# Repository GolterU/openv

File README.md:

### Heizungssteuerung und -überwachung per Optolink-Schnittstelle
Für die Windows-Software ["Viess-ion"](https://github.com/openv/openv/wiki/Vies-sion) werden hier die passenden Parameter-Dateien bearbeitet, damit sie zur Heizungsanlage passen. Die Kommunikation zwischen Steuer-PC und der Heizung erfolgt mithilfe des Adapters ["Optolink-Duo/Sniffer"](https://github.com/openv/openv/wiki/Bauanleitung-USB_Duo-Sniffer).<p>
Die Heizungsanlage besteht aus dem Gaswandgerät "Vitodens 300-W" WB3C, Code: CB und zwei Heizkreisen. <br>
Kreis A1 für die Heizkörper hängt über die interne Heizungspumpe direkt am Kessel. Kreis M2 für die Räume mit Fußbodenheizung über einen Drei-Wege-Mischer, der am KM-Bus angeschlossen ist. Es wird zusätzlich ein 300-Liter-Boiler zur Warmwasserbereitung betrieben. Die Warmwasserverteilung im Haus erfolgt mit Hilfe einer zeitgesteuerten Zirkulationspumpe, die ihrerseits an der externen Erweiterung H1 hängt.<br>
Die Heizungssteuerung erfolgt intern mit der herstellereigenen Vitotronic. Die Heizkreise des Hauses jedoch über eine selbstentwickelte Steuerung ["HSC"](https://godemann.de/Controller/Hauscomputer/hauscomputer.html), die ohne Eingriff in die Heizungssteuerung auskommt.

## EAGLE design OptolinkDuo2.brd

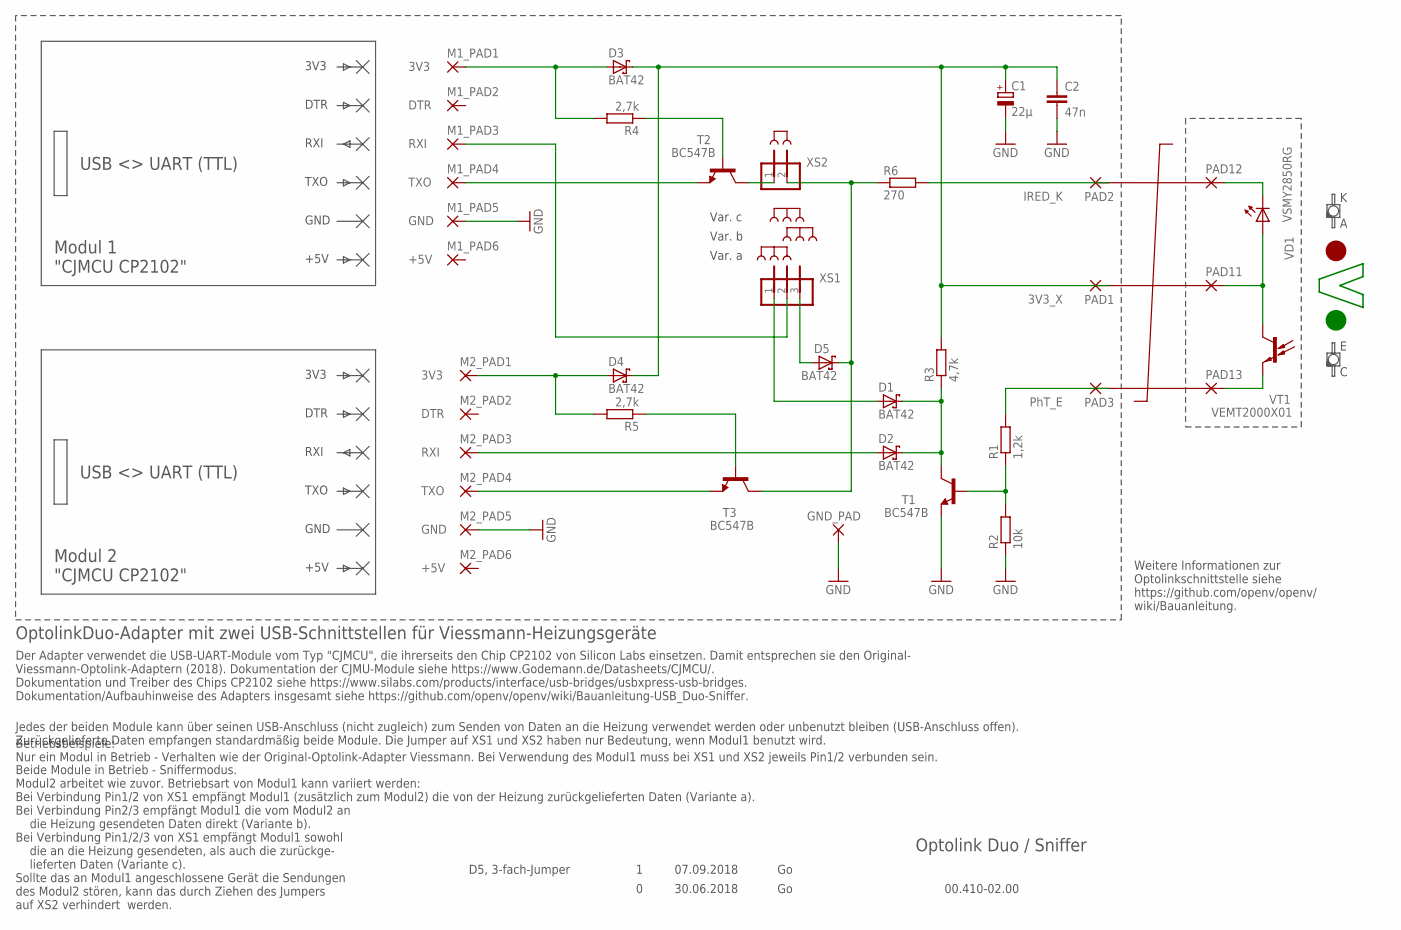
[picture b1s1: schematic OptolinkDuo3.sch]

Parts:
3V3_XE: V; V-PAC
C1: 22µ; E2,5-5
C2: 47n; C050-024X044
D1, D2, D3, D4, D5: BAT42; DO35-10
GND_PAD: GND; 2,15/1,0
J1, J2: JUMPER; JUMP
M1_PAD1, M2_PAD1: 3V3; 2,15/1,0
M1_PAD2, M2_PAD2: DTR; 2,15/1,0
M1_PAD3, M2_PAD3: RXI; 2,15/1,0
M1_PAD4, M2_PAD4: TXO; 2,15/1,0
M1_PAD5, M2_PAD5: GND; 2,15/1,0
M1_PAD6, M2_PAD6: +5V; 2,15/1,0
PAD1: 3V3_X; 1,6/0,8
PAD2: IRED_K; 1,6/0,8
PAD3: PhT_E; 1,6/0,8
PAD11: 3V3_x; SMD1,27-2,54
PAD12: IRED_K; SMD1,27-2,54
PAD13: PhT_E; SMD1,27-2,54
R1: 1,2k; 0207/10
R2: 10k; 0207/10
R3: 4,7k; 0207/10
R4, R5: 2,7k; 0207/10
R6: 270; 0207/10
T1, T2, T3: BC547B; TO92-CBE
VD1: VSMY2850RG; VISHAY_GULLWING(R)
VT1: VEMT2000X01; VISHAY_GULLWING(R)
XS1: PINHD-1X3; 1X03
XS2: PINHD-1X2; 1X02

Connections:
3V3_1: D3.A, M1_PAD1.1, R4.2
3V3_2: D4.A, M2_PAD1.1, R5.2
3V3_X: C1.+, C2.1, D3.C, D4.C, PAD1.1, R3.2
3V3_XE: PAD11.1, VD1.COLLECTOR (A), VT1.COLLECTOR (C)
GND: C1.-, C2.2, GND_PAD.1, M1_PAD5.1, M2_PAD5.1, R2.1, T1.E
unnamed: T2.C, XS2.1
unnamed: D2.A, M2_PAD3.1
unnamed: D1.A, XS1.1
unnamed: D5.C, R6.1, T3.C, XS2.2
unnamed: PAD12.1, VD1.EMITTER (C)
unnamed: PAD13.1, VT1.EMITTER (E)
unnamed: D5.A, XS1.3
unnamed: PAD3.1, R1.2
unnamed: R1.1, R2.2, T1.B
unnamed: D1.C, D2.C, R3.1, T1.C
unnamed: M1_PAD3.1, XS1.2
unnamed: R5.1, T3.B
unnamed: R4.1, T2.B
unnamed: PAD2.1, R6.2
TXO_1: M1_PAD4.1, T2.E
TXO_2: M2_PAD4.1, T3.E

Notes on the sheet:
Optolink Duo / Sniffer
00.410-02.00
Modul 1 "CJMCU CP2102"
3V3
DTR
RXI
TXO
GND
+5V
USB <> UART (TTL)
Modul 2 "CJMCU CP2102"
30.06.2018
OptolinkDuo-Adapter mit zwei USB-Schnittstellen für Viessmann-Heizungsgeräte
Der Adapter verwendet die USB-UART-Module vom Typ "CJMCU", die ihrerseits den Chip CP2102 von Silicon Labs einsetzen. Damit entsprechen sie den Original- Viessmann-Optolink-Adaptern (2018). Dokumentation der CJMU-Module siehe https://www.Godemann.de/Datasheets/CJMCU/. Dokumentation und Treiber des 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
Beide Module in Betrieb - Sniffermodus. Modul2 arbeitet wie zuvor. Betriebsart von Modul1 kann variiert werden: Bei Verbindung Pin1/2 von XS1 empfängt Modul1 (zusätzlich zum Modul2) die von der Heizung zurückgelieferten Daten (Variante a). Bei Verbindung Pin2/3 empfängt Modul1 die vom Modul2 an die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
Jedes der beiden Module kann über seinen USB-Anschluss (nicht zugleich) zum Senden von Daten an die Heizung verwendet werden oder unbenutzt bleiben (USB-Anschluss offen). Zurückgelieferte Daten empfangen standardmäßig beide Module. Die Jumper auf XS1 und XS2 haben nur Bedeutung, wenn Modul1 benutzt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
Weitere Informationen zur Optolinkschnittstelle siehe https://github.com/openv/openv/ wiki/Bauanleitung.
07.09.2018
D5, 3-fach-Jumper
Betriebsbeispiele: Nur ein Modul in Betrieb - Verhalten wie der Original-Optolink-Adapter Viessmann. Bei Verwendung des Modul1 muss bei XS1 und XS2 jeweils Pin1/2 verbunden sein.
Var. a
Var. b
Var. c

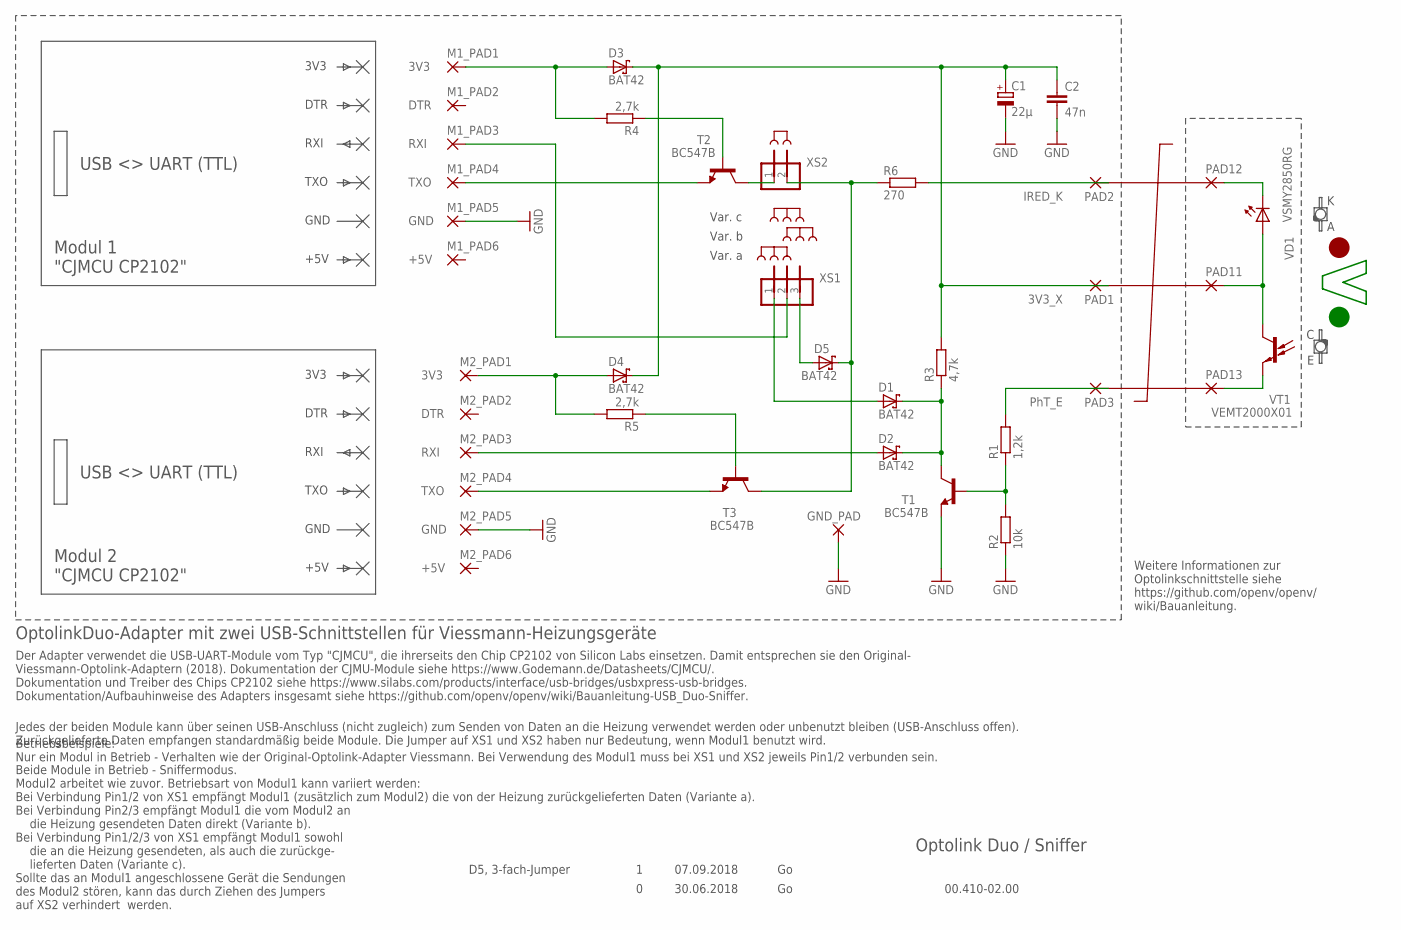
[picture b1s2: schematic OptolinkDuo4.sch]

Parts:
3V3_XE: V; V-PAC
C1: 22µ; E2,5-5
C2: 47n; C050-024X044
D1, D2, D3, D4, D5: BAT42; DO35-10
GND_PAD: GND; 2,15/1,0
J1, J2: JUMPER; JUMP
M1_PAD1, M2_PAD1: 3V3; 2,15/1,0
M1_PAD2, M2_PAD2: DTR; 2,15/1,0
M1_PAD3, M2_PAD3: RXI; 2,15/1,0
M1_PAD4, M2_PAD4: TXO; 2,15/1,0
M1_PAD5, M2_PAD5: GND; 2,15/1,0
M1_PAD6, M2_PAD6: +5V; 2,15/1,0
PAD1: 3V3_X; 1,6/0,8
PAD2: IRED_K; 1,6/0,8
PAD3: PhT_E; 1,6/0,8
PAD11: 3V3_x; SMD1,27-2,54
PAD12: IRED_K; SMD1,27-2,54
PAD13: PhT_E; SMD1,27-2,54
R1: 1,2k; 0207/10
R2: 10k; 0207/10
R3: 4,7k; 0207/10
R4, R5: 2,7k; 0207/10
R6: 270; 0207/10
T1, T2, T3: BC547B; TO92-CBE
VD1: VSMY2850RG; VISHAY_GULLWING(R)
VT1: VEMT2000X01; VISHAY_GULLWING(R)
XS1: PINHD-1X3; 1X03
XS2: PINHD-1X2; 1X02

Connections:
3V3_1: D3.A, M1_PAD1.1, R4.2
3V3_2: D4.A, M2_PAD1.1, R5.2
3V3_X: C1.+, C2.1, D3.C, D4.C, PAD1.1, R3.2
3V3_XE: PAD11.1, VD1.COLLECTOR (A), VT1.COLLECTOR (C)
GND: C1.-, C2.2, GND_PAD.1, M1_PAD5.1, M2_PAD5.1, R2.1, T1.E
unnamed: T2.C, XS2.1
unnamed: D2.A, M2_PAD3.1
unnamed: D1.A, XS1.1
unnamed: D5.C, R6.1, T3.C, XS2.2
unnamed: PAD12.1, VD1.EMITTER (C)
unnamed: PAD13.1, VT1.EMITTER (E)
unnamed: D5.A, XS1.3
unnamed: PAD3.1, R1.2
unnamed: R1.1, R2.2, T1.B
unnamed: D1.C, D2.C, R3.1, T1.C
unnamed: M1_PAD3.1, XS1.2
unnamed: R5.1, T3.B
unnamed: R4.1, T2.B
unnamed: PAD2.1, R6.2
TXO_1: M1_PAD4.1, T2.E
TXO_2: M2_PAD4.1, T3.E

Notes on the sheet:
Optolink Duo / Sniffer
00.410-02.00
Modul 1 "CJMCU CP2102"
3V3
DTR
RXI
TXO
GND
+5V
USB <> UART (TTL)
Modul 2 "CJMCU CP2102"
30.06.2018
OptolinkDuo-Adapter mit zwei USB-Schnittstellen für Viessmann-Heizungsgeräte
Der Adapter verwendet die USB-UART-Module vom Typ "CJMCU", die ihrerseits den Chip CP2102 von Silicon Labs einsetzen. Damit entsprechen sie den Original- Viessmann-Optolink-Adaptern (2018). Dokumentation der CJMU-Module siehe https://www.Godemann.de/Datasheets/CJMCU/. Dokumentation und Treiber des 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
Beide Module in Betrieb - Sniffermodus. Modul2 arbeitet wie zuvor. Betriebsart von Modul1 kann variiert werden: Bei Verbindung Pin1/2 von XS1 empfängt Modul1 (zusätzlich zum Modul2) die von der Heizung zurückgelieferten Daten (Variante a). Bei Verbindung Pin2/3 empfängt Modul1 die vom Modul2 an die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
Jedes der beiden Module kann über seinen USB-Anschluss (nicht zugleich) zum Senden von Daten an die Heizung verwendet werden oder unbenutzt bleiben (USB-Anschluss offen). Zurückgelieferte Daten empfangen standardmäßig beide Module. Die Jumper auf XS1 und XS2 haben nur Bedeutung, wenn Modul1 benutzt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
Weitere Informationen zur Optolinkschnittstelle siehe https://github.com/openv/openv/ wiki/Bauanleitung.
07.09.2018
D5, 3-fach-Jumper
Betriebsbeispiele: Nur ein Modul in Betrieb - Verhalten wie der Original-Optolink-Adapter Viessmann. Bei Verwendung des Modul1 muss bei XS1 und XS2 jeweils Pin1/2 verbunden sein.
Var. a
Var. b
Var. c

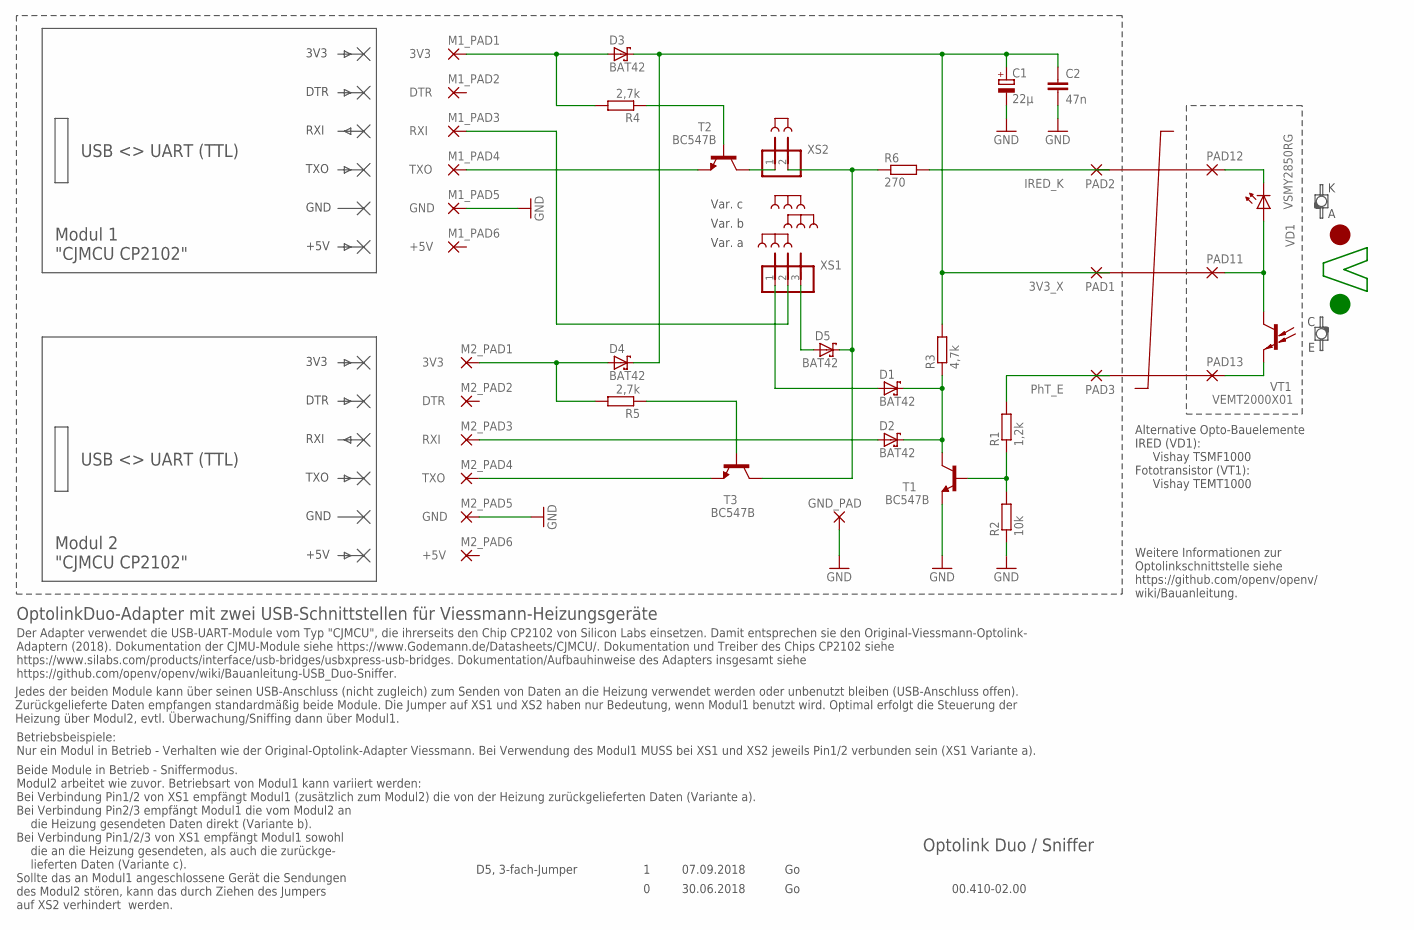
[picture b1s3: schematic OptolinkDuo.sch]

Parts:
3V3_XE: V; V-PAC
C1: 22µ; E2,5-5
C2: 47n; C050-024X044
D1, D2, D3, D4, D5: BAT42; DO35-10
GND_PAD: GND; 2,15/1,0
J1, J2: JUMPER; JUMP
M1_PAD1, M2_PAD1: 3V3; 2,15/1,0
M1_PAD2, M2_PAD2: DTR; 2,15/1,0
M1_PAD3, M2_PAD3: RXI; 2,15/1,0
M1_PAD4, M2_PAD4: TXO; 2,15/1,0
M1_PAD5, M2_PAD5: GND; 2,15/1,0
M1_PAD6, M2_PAD6: +5V; 2,15/1,0
PAD1: 3V3_X; 1,6/0,8
PAD2: IRED_K; 1,6/0,8
PAD3: PhT_E; 1,6/0,8
PAD11: 3V3_x; SMD1,27-2,54
PAD12: IRED_K; SMD1,27-2,54
PAD13: PhT_E; SMD1,27-2,54
R1: 1,2k; 0207/10
R2: 10k; 0207/10
R3: 4,7k; 0207/10
R4, R5: 2,7k; 0207/10
R6: 270; 0207/10
T1, T2, T3: BC547B; TO92-CBE
VD1: VSMY2850RG; VISHAY_GULLWING(R)
VT1: VEMT2000X01; VISHAY_GULLWING(R)
XS1: PINHD-1X3; 1X03
XS2: PINHD-1X2; 1X02

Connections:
3V3_1: D3.A, M1_PAD1.1, R4.2
3V3_2: D4.A, M2_PAD1.1, R5.2
3V3_X: C1.+, C2.1, D3.C, D4.C, PAD1.1, R3.2
3V3_XE: PAD11.1, VD1.COLLECTOR (A), VT1.COLLECTOR (C)
GND: C1.-, C2.2, GND_PAD.1, M1_PAD5.1, M2_PAD5.1, R2.1, T1.E
unnamed: T2.C, XS2.1
unnamed: D2.A, M2_PAD3.1
unnamed: D1.A, XS1.1
unnamed: D5.C, R6.1, T3.C, XS2.2
unnamed: PAD12.1, VD1.EMITTER (C)
unnamed: PAD13.1, VT1.EMITTER (E)
unnamed: D5.A, XS1.3
unnamed: PAD3.1, R1.2
unnamed: R1.1, R2.2, T1.B
unnamed: D1.C, D2.C, R3.1, T1.C
unnamed: M1_PAD3.1, XS1.2
unnamed: R5.1, T3.B
unnamed: R4.1, T2.B
unnamed: PAD2.1, R6.2
TXO_1: M1_PAD4.1, T2.E
TXO_2: M2_PAD4.1, T3.E

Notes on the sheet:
Optolink Duo / Sniffer
00.410-02.00
Modul 1 "CJMCU CP2102"
3V3
DTR
RXI
TXO
GND
+5V
USB <> UART (TTL)
Modul 2 "CJMCU CP2102"
30.06.2018
OptolinkDuo-Adapter mit zwei USB-Schnittstellen für Viessmann-Heizungsgeräte
Der Adapter verwendet die USB-UART-Module vom Typ "CJMCU", die ihrerseits den Chip CP2102 von Silicon Labs einsetzen. Damit entsprechen sie den Original-Viessmann-Optolink- Adaptern (2018). Dokumentation der CJMU-Module siehe https://www.Godemann.de/Datasheets/CJMCU/. Dokumentation und Treiber des 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
Beide Module in Betrieb - Sniffermodus. Modul2 arbeitet wie zuvor. Betriebsart von Modul1 kann variiert werden: Bei Verbindung Pin1/2 von XS1 empfängt Modul1 (zusätzlich zum Modul2) die von der Heizung zurückgelieferten Daten (Variante a). Bei Verbindung Pin2/3 empfängt Modul1 die vom Modul2 an die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
Jedes der beiden Module kann über seinen USB-Anschluss (nicht zugleich) zum Senden von Daten an die Heizung verwendet werden oder unbenutzt bleiben (USB-Anschluss offen). Zurückgelieferte Daten empfangen standardmäßig beide Module. Die Jumper auf XS1 und XS2 haben nur Bedeutung, wenn Modul1 benutzt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
Weitere Informationen zur Optolinkschnittstelle siehe https://github.com/openv/openv/ wiki/Bauanleitung.
07.09.2018
D5, 3-fach-Jumper
Betriebsbeispiele: Nur ein Modul in Betrieb - Verhalten wie der Original-Optolink-Adapter Viessmann. Bei Verwendung des Modul1 MUSS bei XS1 und XS2 jeweils Pin1/2 verbunden sein (XS1 Variante a).
Var. a
Var. b
Var. c
Alternative Opto-Bauelemente IRED (VD1): Vishay TSMF1000 Fototransistor (VT1): Vishay TEMT1000

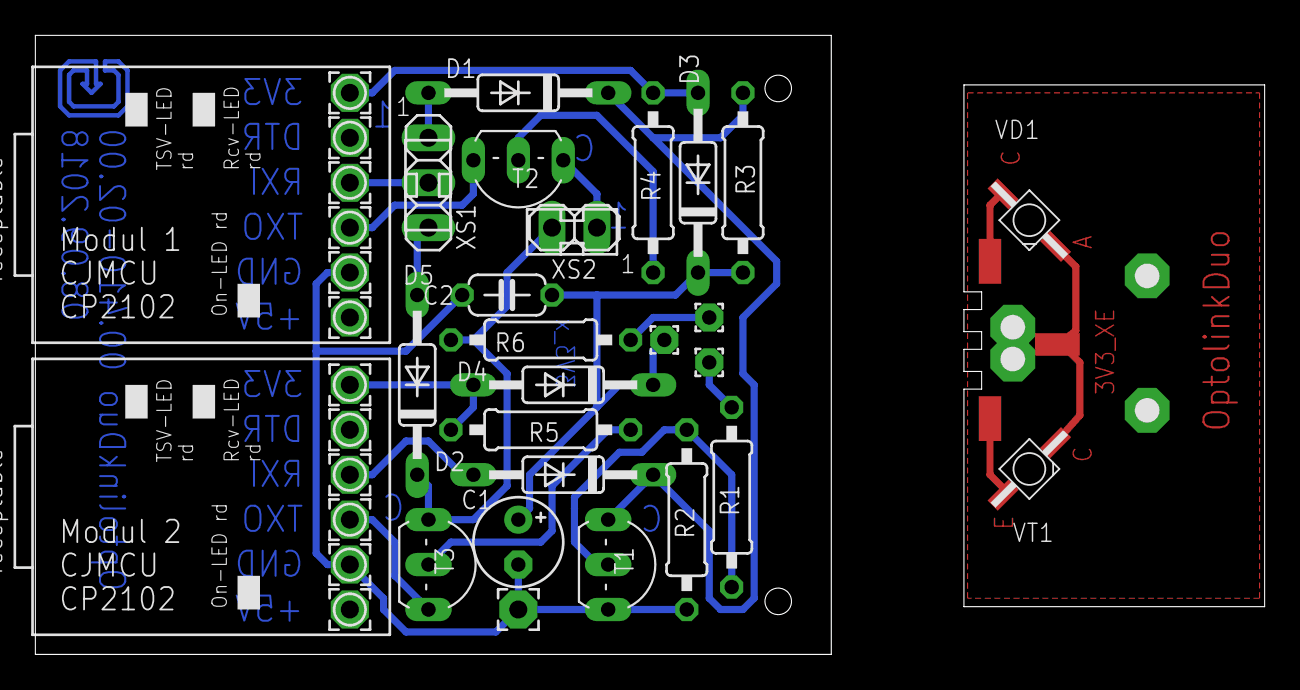
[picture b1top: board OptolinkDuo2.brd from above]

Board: 2 copper layers, 69.5 x 35.0 mm, 43 parts (0 on the bottom side), 21 nets.

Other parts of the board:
U$4: !G-SIGN_B

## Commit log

2018-09-25 Rename OptolinkDuo.sch to OptolinkDuo4.sch
2018-11-30 Rename OptolinkDuo.sch to OptolinkDuo5.sch
2019-02-09 Änderungen XML-Datei bis 24.04.18 21:53
2019-02-09 Änderungen ..CB.xml bis 27.01.19 22:44 Uhr
2019-02-09 Historie bis 09.02.19
2019-02-10 Unnötige Dateien gelöscht
2019-02-10 Historie wieder dazu
2019-02-10 Stand 09.02.19 23:22 Uhr
2019-02-11 Nur Standdatum korrigiert
2019-02-11 "Raum Temperatur Ist-Wert" (0898) aus Kat. Sensor entfernt
2019-02-11 11.02.19 17:45
2019-03-08 Update Historie_Viess-ion_CB.xml.txt
    Hinweis zu <check>
2019-05-18 Änderungen Adr 3302/3303/0842
2019-05-26 s. Historie_Viess-ion_CB
